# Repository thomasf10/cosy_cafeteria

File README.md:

# cosy cafeteria: project embedded systems design 2 
This repository contains the developed software and hardware for the lab project of embedded systems design 2.

## Structure
- [Software](Software)
  * [Python server script](Software/python_wifi/WiFi.py)
  * [ESP32 code](Software/fullcode)
- [Hardware](Hardware)
  * [Main PCB](Hardware/MainPCB)
  * [Sensor PCB](Hardware/SesnorBoard)
- [Website/Dashboard](Dashboard)
- [Report](Report/Report.pdf)

## Project discription
To  improve  the  experience  of  the  students  in  the  cafeteria,  an  embeddedsystem will be developed to gather a variety of data.  This data will then bedisplay to the students through an online medium such as a website.  Themain focus will be to gather information about the amount of people thatare in the cafeteria. There are two main goals. The first goal is to display theestimated waiting time to get a meal to the students.  Secondly the amountof available seats will be tracked and displayed to the students.  Next to thissome additional information will be gathered.  The temperature, air-qualityand sound level will be monitored to give the student a general idea about theconditions in the cafeteria.  This way the student can gauge if the cafeteriais suitable to study in at a certain moment.  An overview of the envisioned system is displayed in the figure bellow.

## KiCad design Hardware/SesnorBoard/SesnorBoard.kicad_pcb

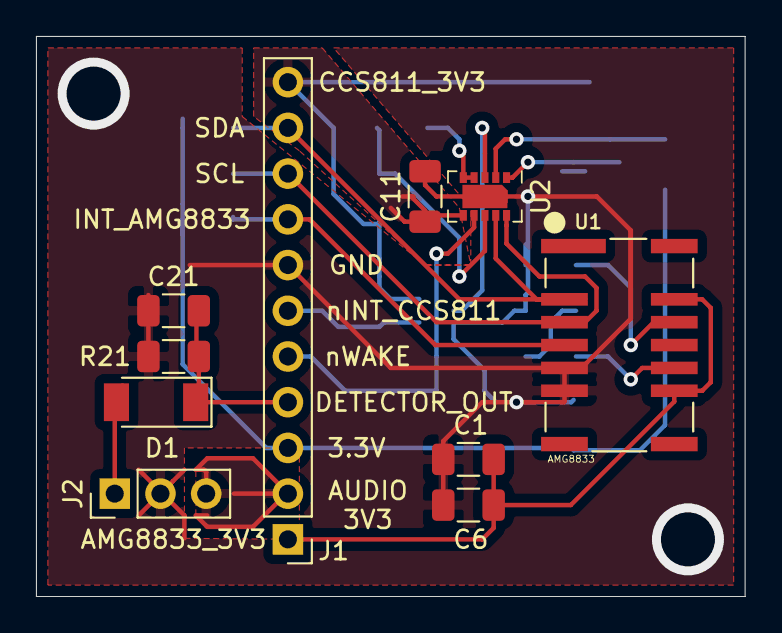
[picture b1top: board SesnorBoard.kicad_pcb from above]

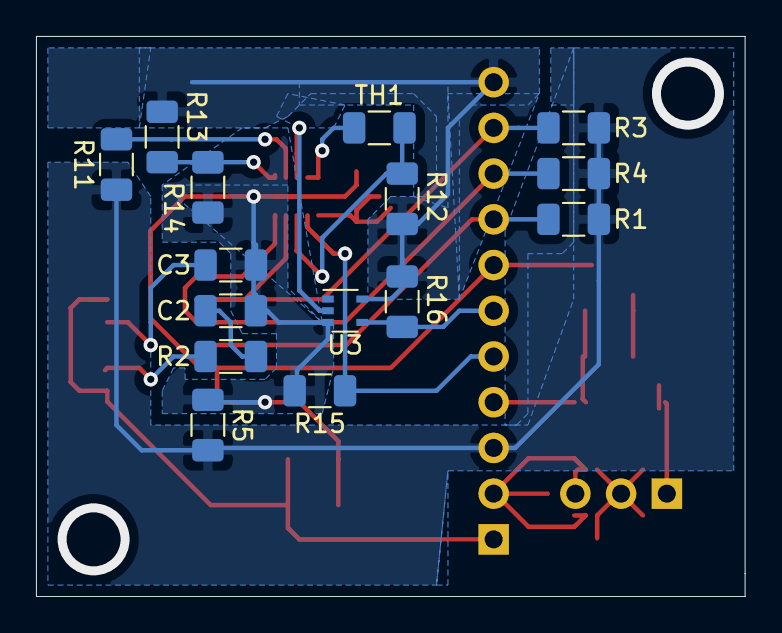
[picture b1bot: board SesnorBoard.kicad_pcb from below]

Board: 2 copper layers, 39.4 x 31.1 mm, 25 parts (15 on the bottom side), 20 nets.

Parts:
C1: 10uF; C_1206_3216Metric
C2: 1uF; C_1206_3216Metric
C3: 2.2uF; C_1206_3216Metric
C6, C21: 0.1uF; C_1206_3216Metric
C11: 4.7µF; C_1206_3216Metric
D1: RB081LAM-20; D_SOD-128
J1: Mainboard connection; PinHeader_1x11_P2.54mm_Vertical
J2: microphoon connection; PinHeader_1x03_P2.54mm_Vertical
R1, R5, R16: 10K; R_1206_3216Metric
R2: 22; R_1206_3216Metric
R3, R4: 2k2; R_1206_3216Metric
R11: 4k7; R_1206_3216Metric
R12, R14: 100k; R_1206_3216Metric
R13: 100K; R_1206_3216Metric
R15: 10k; R_1206_3216Metric
R21: 1M; R_1206_3216Metric
TH1: 100K; R_1206_3216Metric
U1: AMG8833
U2: CCS811; AMS_LGA-10-1EP_2.7x4mm_P0.6mm
U3: NC7SVU04P5X; SOT-353_SC-70-5

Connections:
3.3V: J1.3, R1.2, R3.2, R4.2, R5.2, R11.1
/AMG8833_3V3: C1.1, C6.1, J1.1, U1.9, U1.13
/AUDIO_3V3: J1.2, J2.3
/AUDIO_OUT: D1.2, J2.1
/CCS811_3V3: C11.1, J1.11, R12.2, R13.2, R16.2, U2.6, U3.5
/DETECTOR_OUT: C21.1, D1.1, J1.4, R21.1
/INT_AMG8833: J1.8, R1.1, U1.4
/SCL: J1.9, R4.1, U1.3, U2.10
/SDA: J1.10, R3.1, U1.2, U2.9
/nINT: U2.3, U3.2
/nINT_CCS811: J1.6, R16.1, U3.4
/nWAKE: J1.5, R15.1, U2.7
GND: C1.2, C3.2, C6.2, C11.2, C21.2, J1.7, J2.2, R2.1, R5.1, R14.1, R15.2, R21.2, U1.5, U1.6, U2.11, U3.3
unnamed: C2.1, U1.10
unnamed: C2.2, R2.2
unnamed: C3.1, U1.12
unnamed: R11.2, U2.2
unnamed: R12.1, TH1.2, U2.8
unnamed: R13.1, R14.2, U2.1
unnamed: TH1.1, U2.4, U2.5

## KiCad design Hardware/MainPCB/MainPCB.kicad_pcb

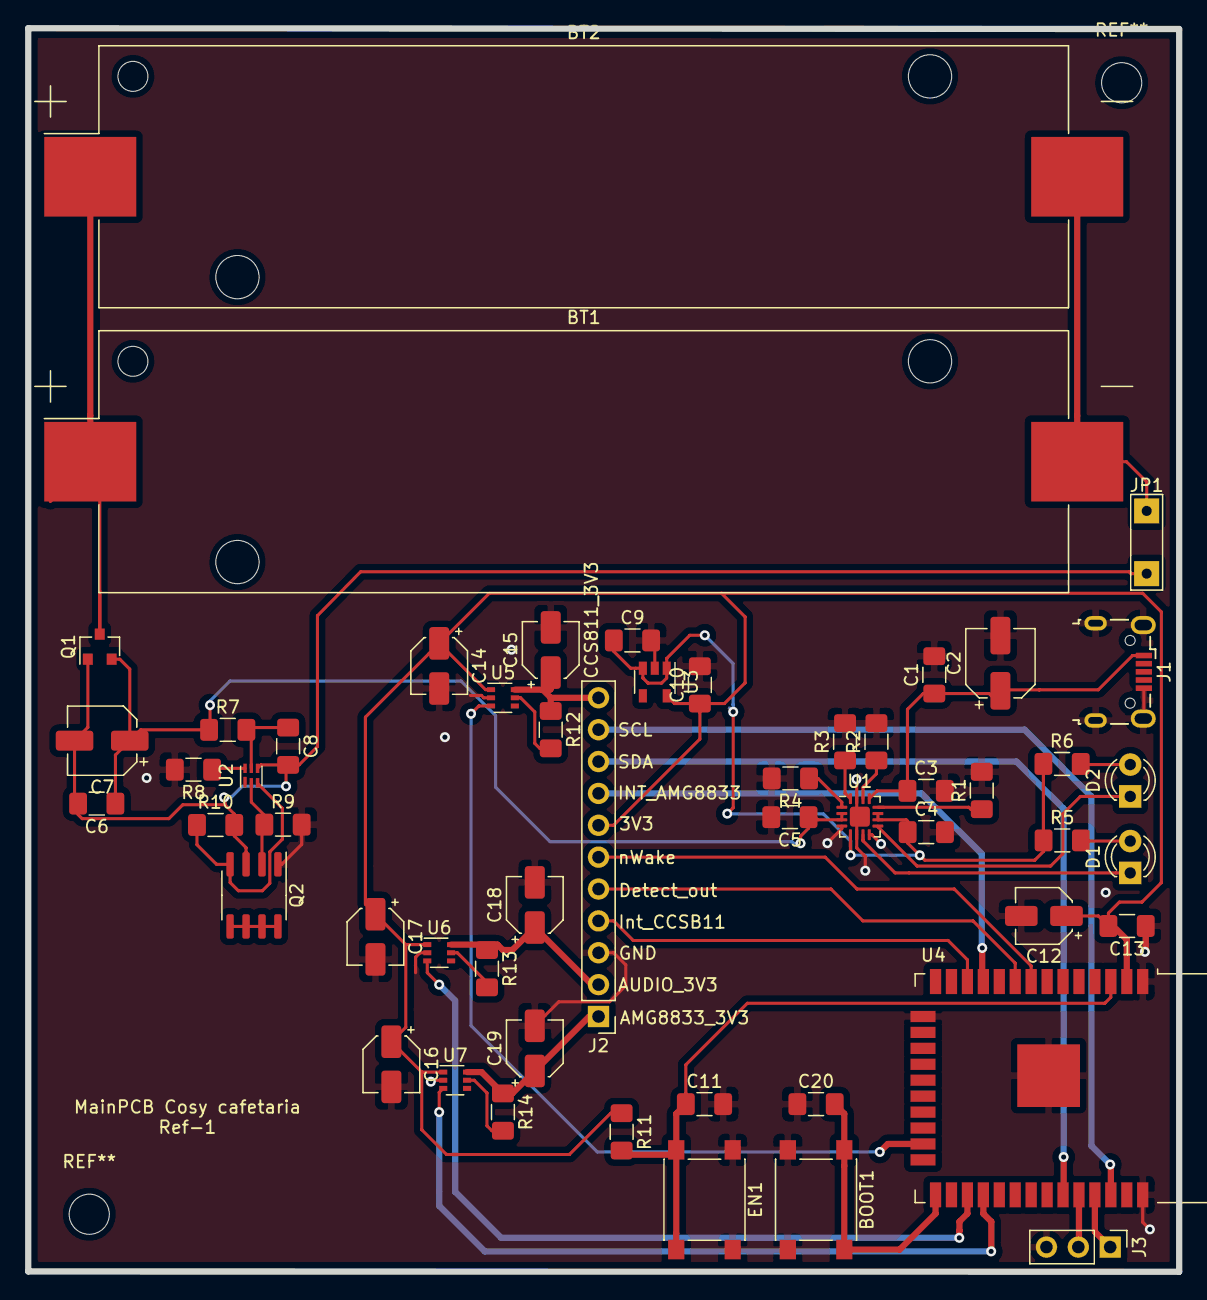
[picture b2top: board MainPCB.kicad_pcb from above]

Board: 2 copper layers, 91.7 x 99.1 mm, 53 parts (0 on the bottom side), 40 nets.

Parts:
BOOT1: SW_DIP_x01; SW_Push_1P1T_NO_6x6mm_H9.5mm
BT1, BT2: Li-ion; BatteryHolder_Keystone_1042_1x18650
C1, C3, C6, C9: 1u; C_1206_3216Metric_Pad1.42x1.75mm_HandSolder
C2, C7: 47u/16V; CP_Elec_5x5.4
C4, C5: 4.7u; C_1206_3216Metric_Pad1.42x1.75mm_HandSolder
C8, C11, C13, C20: 0.1u; C_1206_3216Metric_Pad1.42x1.75mm_HandSolder
C10: 47u/10V; C_1206_3216Metric_Pad1.42x1.75mm_HandSolder
C12, C15, C18, C19: 10u/16V; CP_Elec_4x5.4
C14, C16, C17: 3.3u/16V; CP_Elec_4x5.4
D1: LED_Green; LED_D3.0mm
D2: LED_Blue; LED_D3.0mm
EN1: SW_DIP_x01; SW_Push_1P1T_NO_6x6mm_H9.5mm
J1: USB_B_Micro; USB_Micro-B_Wuerth_629105150521
J2: Conn_01x11; PinHeader_1x11_P2.54mm_Vertical
J3: UART; PinHeader_1x03_P2.54mm_Vertical
JP1: Stroommeetdraad; Wire
Q1: NTR2101P; SOT-23
Q2: FDS9926A; SOIC-8_3.9x4.9mm_P1.27mm
R1: 1.1k; R_1206_3216Metric_Pad1.42x1.75mm_HandSolder
R2: 47k; R_1206_3216Metric_Pad1.42x1.75mm_HandSolder
R3, R12, R13, R14: 680; R_1206_3216Metric_Pad1.42x1.75mm_HandSolder
R4, R11: 10k; R_1206_3216Metric_Pad1.42x1.75mm_HandSolder
R5, R6: 1.5k; R_1206_3216Metric_Pad1.42x1.75mm_HandSolder
R7: 330; R_1206_3216Metric_Pad1.42x1.75mm_HandSolder
R8: 2.2k; R_1206_3216Metric_Pad1.42x1.75mm_HandSolder
R9, R10: 5 Meg; R_1206_3216Metric_Pad1.42x1.75mm_HandSolder
U1: BQ24075; VQFN-16-1EP_3x3mm_P0.5mm_EP1.6x1.6mm
U2: BQ29700; WSON-6_1.5x1.5mm_P0.5mm
U3: TLV75533PDBV; SOT-23-5
U4: ESP32-WROOM-32D; ESP32-WROOM-32
U5, U6, U7: TPS22919; SOT-363_SC-70-6

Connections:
+3V3: C10.1, C12.1, C13.2, C14.1, C16.1, C17.1, J2.7, R11.1, U3.5, U4.2, U5.1, U6.1, U7.1
+BATT: BT1.1, BT2.1, Q1.3
-BATT: C6.2, C7.2, C8.2, JP1.2, Q1.1, Q2.3, R10.2, U2.4
AMG8833_3V3: C19.1, J2.1, R14.1, U7.6
AUDIO_3V3: C18.1, J2.2, R13.1, U6.6
CCS811_3V3: C15.1, J2.11, R12.1, U5.6
Detector_out: J2.5, U4.9
GND: BOOT1.2, C1.2, C2.2, C3.2, C4.2, C5.2, C9.2, C10.2, C11.2, C12.2, C13.1, C14.2, C15.2, C16.2, C17.2, C18.2, C19.2, C20.1, EN1.1, J1.5, J1.6, J2.3, J3.3, Q2.1, R1.2, R2.2, R3.2, R4.2, R8.2, R9.2, U1.4, U1.6, U1.8, U1.15, U1.17, U3.2, U4.1, U4.15, U4.38, U4.39, U5.2, U6.2, U7.2
Int_AMG8833: J2.8, U4.11
Int_CCSB11: J2.4, U4.12
unnamed: BOOT1.1, C20.2, U4.25
unnamed: BT1.2, BT2.2, JP1.1
unnamed: C8.1, R7.2, U2.5
unnamed: C11.1, EN1.2, R11.2, U4.3
unnamed: D1.1, U1.7
unnamed: D1.2, R5.2
unnamed: D2.1, U1.9
unnamed: D2.2, R6.2
unnamed: J3.1, U4.35
unnamed: J3.2, U4.34
unnamed: Q2.2, R9.1, U2.2
unnamed: Q2.4, R10.1, U2.3
unnamed: Q2.5, Q2.6, Q2.7, Q2.8
unnamed: R1.1, U1.12
unnamed: R2.1, U1.14
unnamed: R3.1, U1.16
unnamed: R4.1, U1.1
unnamed: R8.1, U2.6
unnamed: R12.2, U5.5
unnamed: R13.2, U6.5
unnamed: R14.2, U7.5
PowerS1: U4.23, U5.3
PowerS2: U4.27, U6.3
PowerS3: U4.28, U7.3
SCL: J2.10, U4.36
SDA: J2.9, U4.33
VDD1: C5.1, C6.1, C7.1, Q1.2, R7.1, U1.2, U1.3
VDD2: C4.1, C9.1, R5.1, R6.1, U1.5, U1.10, U1.11, U3.1, U3.3
Vin: C1.1, C2.1, C3.1, J1.1, U1.13
nWake: J2.6, U4.8

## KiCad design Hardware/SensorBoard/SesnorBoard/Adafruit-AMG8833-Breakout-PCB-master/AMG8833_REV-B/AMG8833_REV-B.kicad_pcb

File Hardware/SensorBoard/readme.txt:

Plaats de PCB voor de sensoren, verwijder gerust. Deze file was nodig voor het aanmaken van de map.

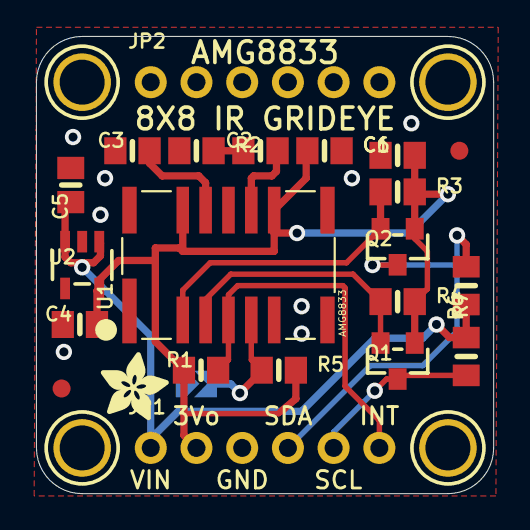
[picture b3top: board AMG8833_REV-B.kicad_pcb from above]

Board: 2 copper layers, 25.4 x 25.4 mm, 28 parts (0 on the bottom side), 12 nets.

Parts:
C1, C4, C5: 10uF; 0805-NO
C2: 1uF; 0805-NO
C3: 2.2uF; 0805-NO
C6: 0.1uF; 0805-NO
FID2, FID3: FIDUCIAL_1MM
JP1, JP2: HEADER-1X670MIL; 1X06_ROUND_70
Q1, Q2: BSS138; SOT23-WIDE
R1, R3, R4, R5: 10K; 0805-NO
R2: 22; 0805-NO
R6, R7: 10K; 0805_10MGAP
SJ1: ADDR; SOLDERJUMPER_ARROW_NOPASTE
U1: AMG8833
U2: mic5225-3.3; SOT23-5
U$16, U$17, U$18, U$19: MOUNTINGHOLE2.5; MOUNTINGHOLE_2.5_PLATED
U$21: ADAFRUIT_3.5MM
U$28: ADAFRUIT_5MM

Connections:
3.3V: C1.1, C4.1, C6.1, JP1.2, Q1.1, Q2.1, R1.2, R3.2, R4.2, R5.2, U1.9, U1.13, U2.5
/INT: JP1.6, R1.1, U1.4
/SCL: JP1.5, Q1.3, R7.1
/SCL_3V: Q1.2, R4.1, U1.3
/SDA: JP1.4, Q2.3, R6.1
/SDA_3V: Q2.2, R3.1, U1.2
GND: C1.2, C3.2, C4.2, C5.1, C6.2, JP1.3, R2.1, SJ1.1, U1.6, U2.2
unnamed: C2.1, U1.10
unnamed: C2.2, R2.2
unnamed: C3.1, U1.12
unnamed: R5.1, SJ1.2, U1.5
VIN: C5.2, JP1.1, R6.2, R7.2, U2.1, U2.3

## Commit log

2020-02-26 Update masterplan
2020-02-27 system architecture
2020-02-28 Add files via upload
    Draft versie van de planning
2020-02-28 Aanmaak MainPCB
2020-02-28 Aanmaken mappen
2020-02-28 Toevoeging BOM excel file
2020-02-28 bom_tobias
2020-02-29 Batterij circuit beslissing genomen
    Beslissing genomen over het oplaad IC, protectie IC, dual N-ch mosfets, batterij. BOM aangepast me 3 verschillende sites bij (farnell, digi-key en mouser). + IC's geplaatst in MainPCB
2020-02-29 Changed battery holder 1043 TH to 1042 SMD
2020-02-29 Toevoeging LDO
2020-03-01 Added milestones to masterplan.tex
2020-03-01 added milestones Robin & Arthur
2020-03-02 Update BOM. Only Mouser links
2020-03-04 Voorblad opgemooid + toevoeging Table of contents
2020-03-04 niets
2020-03-04 toevoeging 2x batterijen BOM
2020-03-04 Toevoeging 1 load switch
2020-03-05 upload sensor board Robin + BOM
2020-03-05 Discrete componenten rond IC's en IC's zelfs nagegaan. + toevoeging BOM
2020-03-05 schematic voor esp32 mainboard
    de esp toegevoegd en de nodige connecties gemaakt
2020-03-06 added buttons to bom
2020-03-06 Main PCB volledig uitgerust met foorprints voor discrete componenten + BOM aangevuld met alles
2020-03-06 Eerste plaatsing van componenten op PCB
2020-03-07 Bom update package 0603 => 1206 sensor board
2020-03-08 Eerste pcb layouts ensorboard
2020-03-09 Aux pin verwijderd + aanpassing gedaan VSS naar -VBAT en GND op de juiste plaats gezet
2020-03-10 SEnsorboard PCB adapted to normal siezd pinheader
2020-03-11 wifi power test
2020-03-11 started layout main pcb
2020-03-12 routed mcu part of main pcb
2020-03-13 probleemke?
2020-03-13 proberen oplossen
2020-03-13 Finished MainPCB + generated gerber files + aanpassingen BOM
2020-03-14 insert pinnames on J1
2020-03-14 Generate gerbers files of sensor board
2020-03-14 Opschonen
2020-03-20 wifi fix: python + esp
2020-03-21 back up sensor board drawing files
2020-03-21 Single core libraries voor ESP32 van op github
2020-03-27 inhoud verslag
2020-03-27 wifi working + state machine code
2020-03-30 grondplan cafetaria
2020-04-03 Aanmaak report
2020-04-03 toevoeging berekeningen charge circuit
2020-04-03 update report
2020-04-03 code update
    - static ip's for wifi => reduces connection time
    - RTC memory => retains variables in deepsleep
    - RTC timer with NTP sync => keeps time
2020-04-07 Begin onderzoek CCS811 optimalisatie uitlezing
    In dit testrapport ga ik na hoe snel we een meting kunnen bekomen van de CCS811 en in een later stadium zijn energie verbruik eraan gekoppeld.
2020-04-10 start website
    finsihed:
    database design
    read data from database
    basic webpage
    todo:
    make it look pretty
2020-04-10 added database
    cosstcafetaria.sql is the file to create the database
2020-04-11 Investigation and basic code sensors complete
    The investgiation on how long it takes for data is avaiable is done.
    Secondly, the basic code with functions for the sensors are completed. This is not yet implemented in a library.
2020-04-11 added heatmap.js
    added heatmap folder
2020-04-12 Onderzoek mensendetectie
    Nog wat resultaten omtrent onze sensoren om mensen te detecteren.
2020-04-15 presentatie
2020-04-15 toevoeging titel + index + power management aan ppt
2020-04-15 update ppt
2020-04-15 ppt KUL stijl
2020-04-15 update pres
2020-04-15 Update tussentijdsepresentatie RVDP
2020-04-16 changed order and added my part
    added main pcb, dashboard
2020-04-16 Adding bom-file for sensor board
    Adding the Bom file as a CSV file in the hardware directory.
2020-04-18 BOM list mainPCB
2020-04-18 Sensorboard toevoeging schematic pdf
2020-04-19 wifi power meting
2020-04-20 start final software
2020-04-20 ability to send floats over wifi added
2020-04-24 sensors and communication addition to main software
    completed:
    - integration of sensor code in main code (has to be tested)
    - transmission of dummy sensor data and processing in python of the
    received data
2020-04-24 full code ready (untested)
2020-04-24 prettyfication of dashboard
2020-04-24 update report
    added:
    -intro
    -functionality
    -wifi discussion
    -state diagram
2020-04-26 Batterij sectie ingevuld + mapjes documentatie over power management herschikt
2020-04-27 aanvulling protection IC
2020-04-28 Power management volledig aangevuld in report
2020-04-29 aanvulling specs en systeem architectuur
2020-04-29 added database access
2020-04-29 added sensor_id + typecasting for sensor_id
2020-04-30 id for nodes
2020-04-30 changed some details
2020-04-30 updated database export
2020-04-30 database update
2020-04-30 Small changes to WiFi.py
2020-04-30 Trying to get json to work
2020-04-30 test 2
2020-04-30 test 3
2020-04-30 test 4
2020-04-30 test 5
2020-04-30 test 6 fingerscrossed
2020-04-30 test 7
2020-04-30 finall push for wifi.py????
2020-04-30 i think this is the one
2020-04-30 the final countdown
2020-04-30 test 13
2020-04-30 test 14
2020-04-30 i'm hopefull it will be the lat commit
2020-04-30 changed database name in database.php
2020-04-30 verbruik metingen
2020-04-30 pwr grafieken
2020-05-01 toevoeging 2e datasheet ncr18650b
2020-05-01 update report
    - software toegevoegd
2020-05-01 battery life berekeningen in verslag
2020-05-01 fix links in readme
2020-05-01 sleep time fix
2020-05-02 Dashboard update
2020-05-02 database change
2020-05-02 Add some 3D-files and start on the sensor part of the report
2020-05-03 updated the sensor part of the report and corrected some issues of the PCB design.
2020-05-04 Dashboard documention started
2020-05-04 updated report
2020-05-04 Text sensor and case done, only images and references need to be added to report for these parts
2020-05-05 Dashboard documentation finished
2020-05-05 review deel robin
2020-05-05 review report
2020-05-05 Figures added sensor part in report
2020-05-06 changed name website to Dashboard
2020-05-06 microcontroller added and started writing about finans
2020-05-06 validation and test
2020-05-06 added financial estimated to report
2020-05-06 aanpassing tabel
2020-05-06 Pictures case and references added at report
2020-05-07 read the report and made corrections where necesarry
2020-05-07 update referenties en vergelijkingen
2020-05-07 final review report
2020-05-07 Update readme.md
    dashboard link fix
2020-05-07 renaming
2020-05-07 final presentation
2020-05-10 contribution Robin parts to final presenation and date update
2020-05-12 ppt update + added video
2020-05-12 update sensoren presentatie
2020-05-12 Aanvulling power management
2020-05-12 Sensor Housing inal presentation
2020-05-13 added text to my slides and finsihed them
2020-05-13 Added some last pictures
2020-05-13 added the schematic sensor
